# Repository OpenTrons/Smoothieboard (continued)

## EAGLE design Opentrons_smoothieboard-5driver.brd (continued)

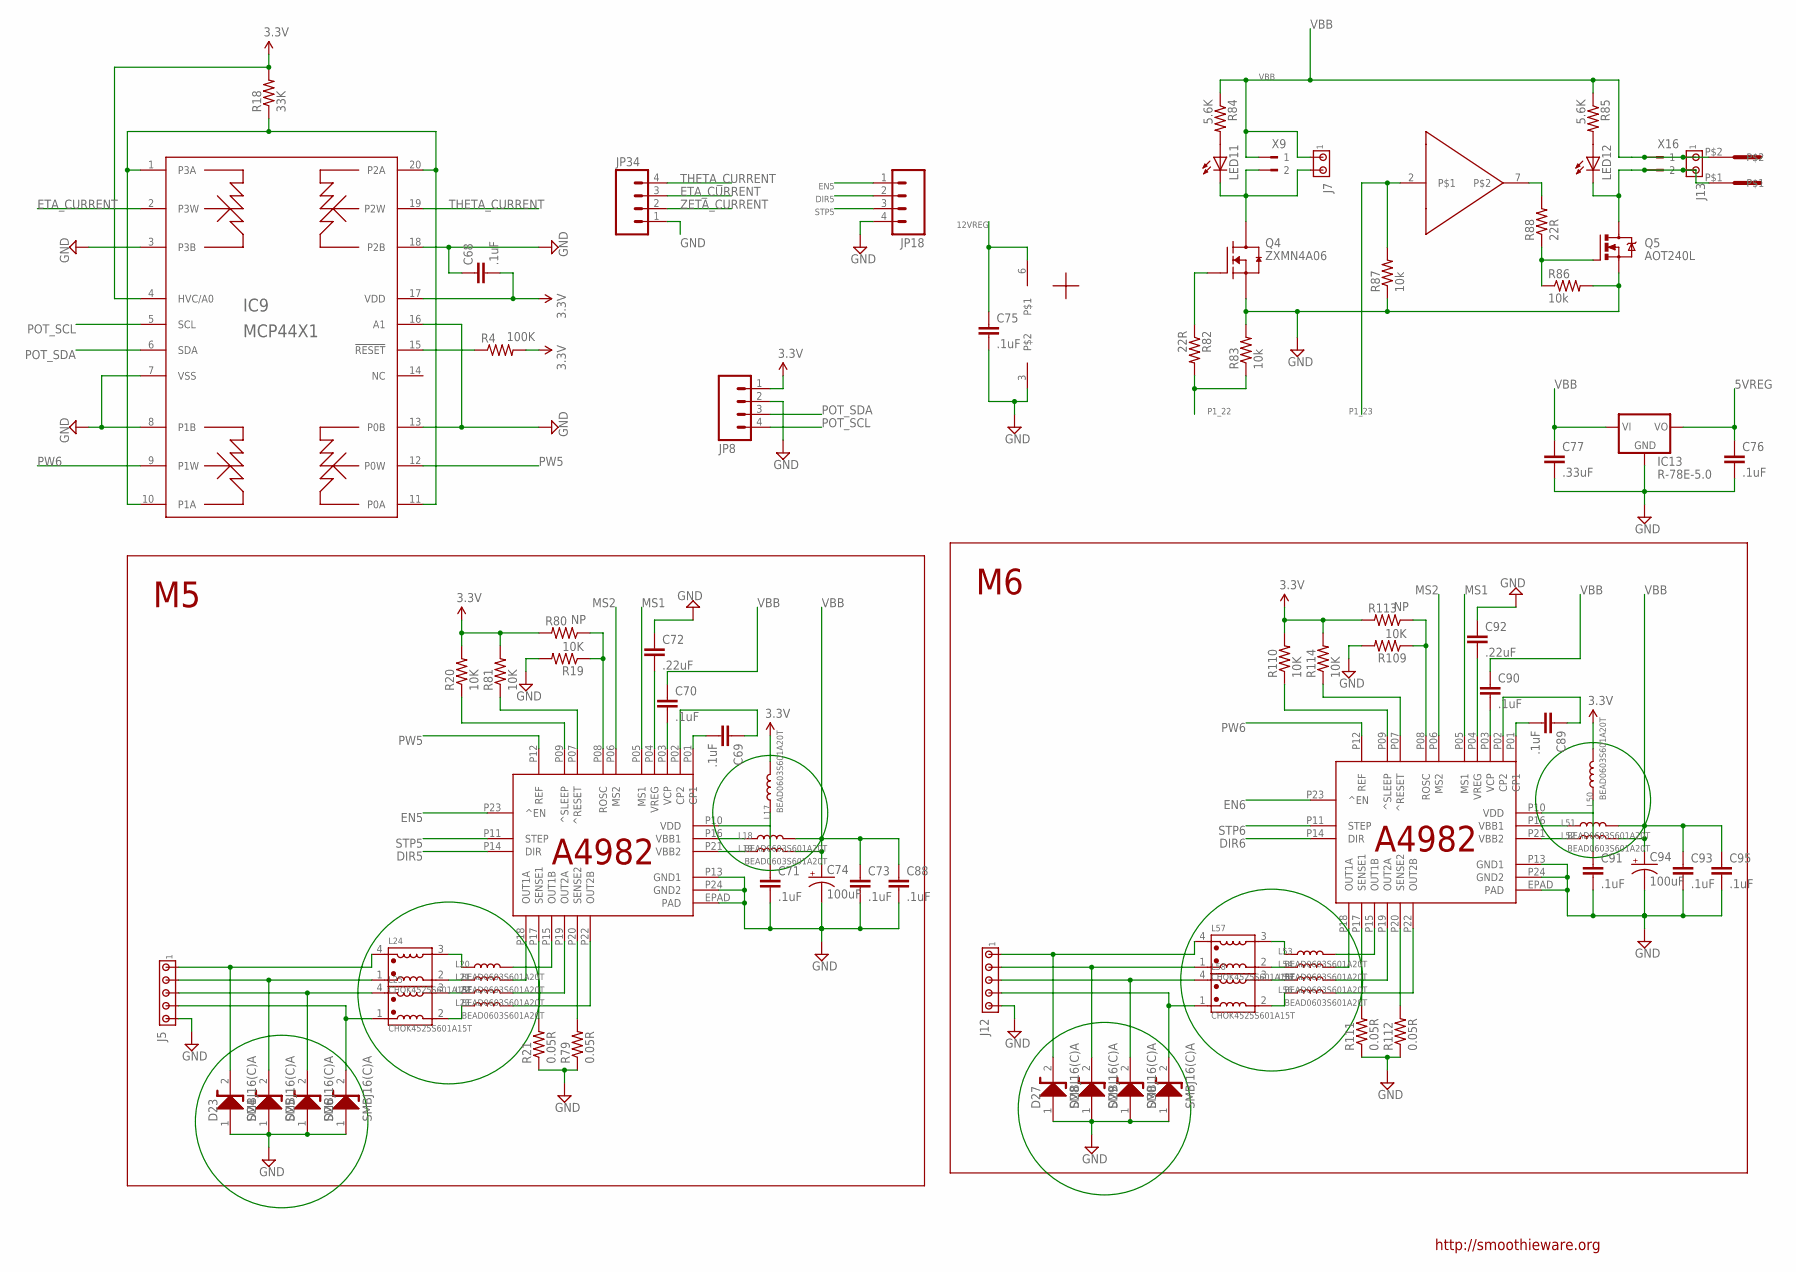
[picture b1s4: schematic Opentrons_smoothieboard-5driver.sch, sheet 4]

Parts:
C68, C69, C70, C71, C73, C75, C76, C88, C89, C90, C91, C93, C95: .1uF; C0603
C72, C92: .22uF; C0603
C74, C94: 100uF; PANASONIC_E
C77: .33uF; C0603
D23, D24, D25, D26, D27, D28, D29, D30: SMBJ16(C)A; DO214-AA_(SMB)
IC9: MCP44X1; TSSOP20
IC12, IC16: A4982; ETSSOP24
IC13: R-78E-5.0; R-78
IC15: TC4427; SOIC8
J5, J12: MTA05-100; 10X05MTA
J7, J13: MTA02-100; 10X02MTA
JP8, JP18, JP34: M041X04_NO_SILK; 1X04_NO_SILK
L17, L18, L19, L20, L21, L22, L23, L50, L51, L52, L53, L54, L55, L56: BEAD0603S601A20T; 0603(1608)
L24, L25, L57, L58: CHOK4525S601A15T; L-4525
LED11, LED12: LEDCHIP-LED0805; CHIP-LED0805
Q4: ZXMN4A06; SOT230P700X160-4N
Q5: AOT240L; TO220BV
R4: 100K; R0603
R18: 33K; R0603
R19, R20, R81, R109, R110, R114: 10K; R0603
R21, R79, R111, R112: 0.05R; R2512
R80, R113: NP; R0603
R82, R88: 22R; R0603
R83, R86, R87: 10k; R0603
R84, R85: 5.6K; R0603
U$7: 5MMCONN; 1715250000
X9, X16: 180G-2

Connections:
3.3V: C68.2, IC9.4 (HVC/A0), IC9.17 (VDD), JP8.1, L17.2, L50.2, R4.2, R18.2, R20.2, R80.2, R81.2, R110.2, R113.2, R114.2; also elsewhere on the board
5VREG: C76.1, IC13.3 (VO); also elsewhere on the board
12VREG: C75.1, IC15.6; also elsewhere on the board
DIR5: IC12.P14 (DIR), JP18.2; also elsewhere on the board
DIR6: IC16.P14 (DIR)
EN5: IC12.P23 (^EN), JP18.1; also elsewhere on the board
EN6: IC16.P23 (^EN)
ETA_CURRENT: IC9.2 (P3W), JP34.3
GND: C68.1, C71.2, C72.1, C73.2, C74.-, C75.2, C76.2, C77.2, C88.2, C91.2, C92.1, C93.2, C94.-, C95.2, D23.1 (A), D24.1 (A), D25.1 (A), D26.1 (A), D27.1 (A), D28.1 (A), D29.1 (A), D30.1 (A), IC9.3 (P3B), IC9.7 (VSS), IC9.8 (P1B), IC9.13 (P0B), IC9.16 (A1), IC9.18 (P2B), IC12.EPAD (PAD), IC12.P13 (GND1), IC12.P24 (GND2), IC13.2 (GND), IC15.3, IC16.EPAD (PAD), IC16.P13 (GND1), IC16.P24 (GND2), J5.5, J12.5, JP8.2, JP18.4, JP34.1, Q4.3 (S), Q5.S, R19.2, R21.1, R79.1, R83.2, R86.2, R87.1, R109.2, R111.1, R112.1; also elsewhere on the board
GPIO_FET1: Q5.G, R86.1, R88.1
J5_1A: D23.2 (K), J5.1, L24.4
J5_1A1: D27.2 (K), J12.1, L57.4
J5_1B: D24.2 (K), J5.2, L24.1
J5_1B1: D28.2 (K), J12.2, L57.1
J5_2A: D25.2 (K), J5.3, L25.4
J5_2A1: D29.2 (K), J12.3, L58.4
J5_2B: D26.2 (K), J5.4, L25.1
J5_2B1: D30.2 (K), J12.4, L58.1
MS1: IC12.P05 (MS1), IC16.P05 (MS1); also elsewhere on the board
MS2: IC12.P06 (MS2), IC16.P06 (MS2); also elsewhere on the board
unnamed: C89.2, IC16.P01 (CP1)
unnamed: IC9.15 (!RESET), R4.1
unnamed: J7.2, LED11.C, Q4.4 (D), X9.2
unnamed: IC9.1 (P3A), IC9.10 (P1A), IC9.11 (P0A), IC9.20 (P2A), R18.1
unnamed: C69.2, IC12.P01 (CP1)
unnamed: C69.1, IC12.P02 (CP2)
unnamed: C70.2, IC12.P03 (VCP)
unnamed: IC12.P17 (SENSE1), R21.2
unnamed: IC12.P20 (SENSE2), R79.2
unnamed: IC12.P18 (OUT1A), L21.2
unnamed: IC12.P15 (OUT1B), L20.2
unnamed: IC12.P19 (OUT2A), L22.2
unnamed: IC12.P22 (OUT2B), L23.2
unnamed: IC12.P08 (ROSC), R19.1, R80.1
unnamed: C72.2, IC12.P04 (VREG)
unnamed: IC12.P09 (^SLEEP), R20.1
unnamed: IC12.P07 (^RESET), R81.1
unnamed: Q4.1 (G), R82.1
unnamed: LED11.A, R84.2
unnamed: J13.2, LED12.C, Q5.D, U$7.P$1, X16.2
unnamed: LED12.A, R85.2
unnamed: IC15.7, R88.2
unnamed: C89.1, IC16.P02 (CP2)
unnamed: C71.1, IC12.P10 (VDD), L17.1
unnamed: IC12.P16 (VBB1), L18.1
unnamed: IC12.P21 (VBB2), L19.1
unnamed: L21.1, L24.2
unnamed: L20.1, L24.3
unnamed: L22.1, L25.3
unnamed: L23.1, L25.2
unnamed: C90.2, IC16.P03 (VCP)
unnamed: IC16.P17 (SENSE1), R111.2
unnamed: IC16.P20 (SENSE2), R112.2
unnamed: IC16.P18 (OUT1A), L54.2
unnamed: IC16.P15 (OUT1B), L53.2
unnamed: IC16.P19 (OUT2A), L55.2
unnamed: IC16.P22 (OUT2B), L56.2
unnamed: IC16.P08 (ROSC), R109.1, R113.1
unnamed: C92.2, IC16.P04 (VREG)
unnamed: IC16.P09 (^SLEEP), R110.1
unnamed: IC16.P07 (^RESET), R114.1
unnamed: C91.1, IC16.P10 (VDD), L50.1
unnamed: IC16.P16 (VBB1), L51.1
unnamed: IC16.P21 (VBB2), L52.1
unnamed: L54.1, L57.2
unnamed: L53.1, L57.3
unnamed: L55.1, L58.3
unnamed: L56.1, L58.2
P1_22: R82.2, R83.1; also elsewhere on the board
P1_23: IC15.2, R87.2; also elsewhere on the board
POT_SCL: IC9.5 (SCL), JP8.4; also elsewhere on the board
POT_SDA: IC9.6 (SDA), JP8.3; also elsewhere on the board
PW5: IC9.12 (P0W), IC12.P12 (REF)
PW6: IC9.9 (P1W), IC16.P12 (REF)
STP5: IC12.P11 (STEP), JP18.3; also elsewhere on the board
STP6: IC16.P11 (STEP)
THETA_CURRENT: IC9.19 (P2W), JP34.4
VBB: C70.1, C73.1, C74.+, C77.1, C88.1, C90.1, C93.1, C94.+, C95.1, IC13.1 (VI), J7.1, J13.1, L18.2, L19.2, L51.2, L52.2, R84.1, R85.1, U$7.P$2, X9.1, X16.1; also elsewhere on the board
ZETA_CURRENT: JP34.2

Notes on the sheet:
http://smoothieware.org

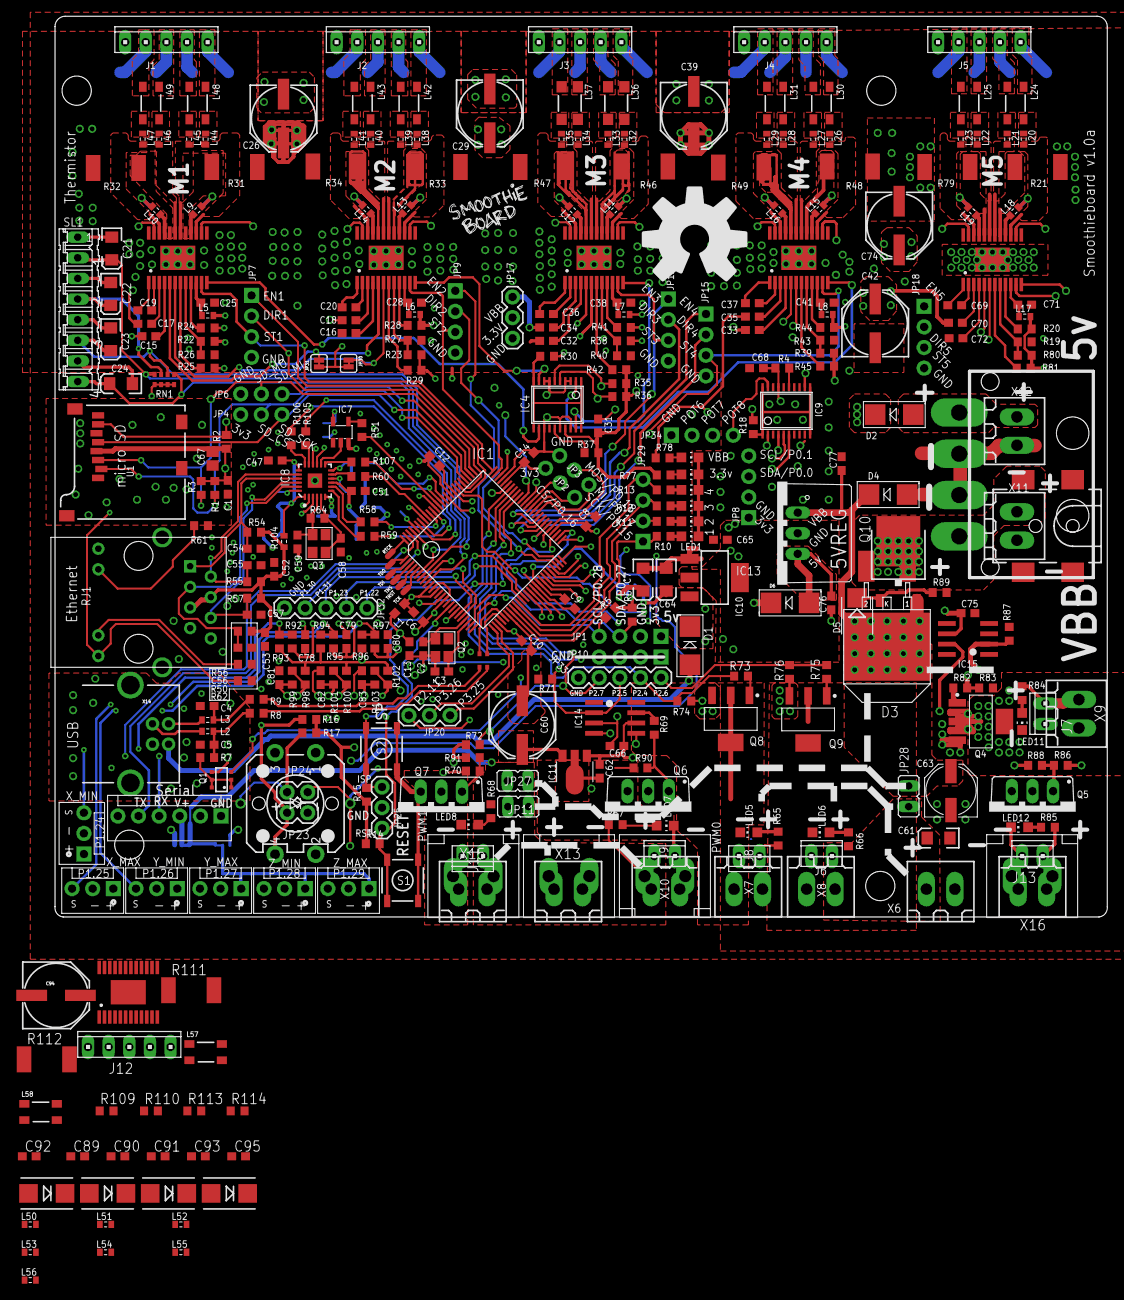
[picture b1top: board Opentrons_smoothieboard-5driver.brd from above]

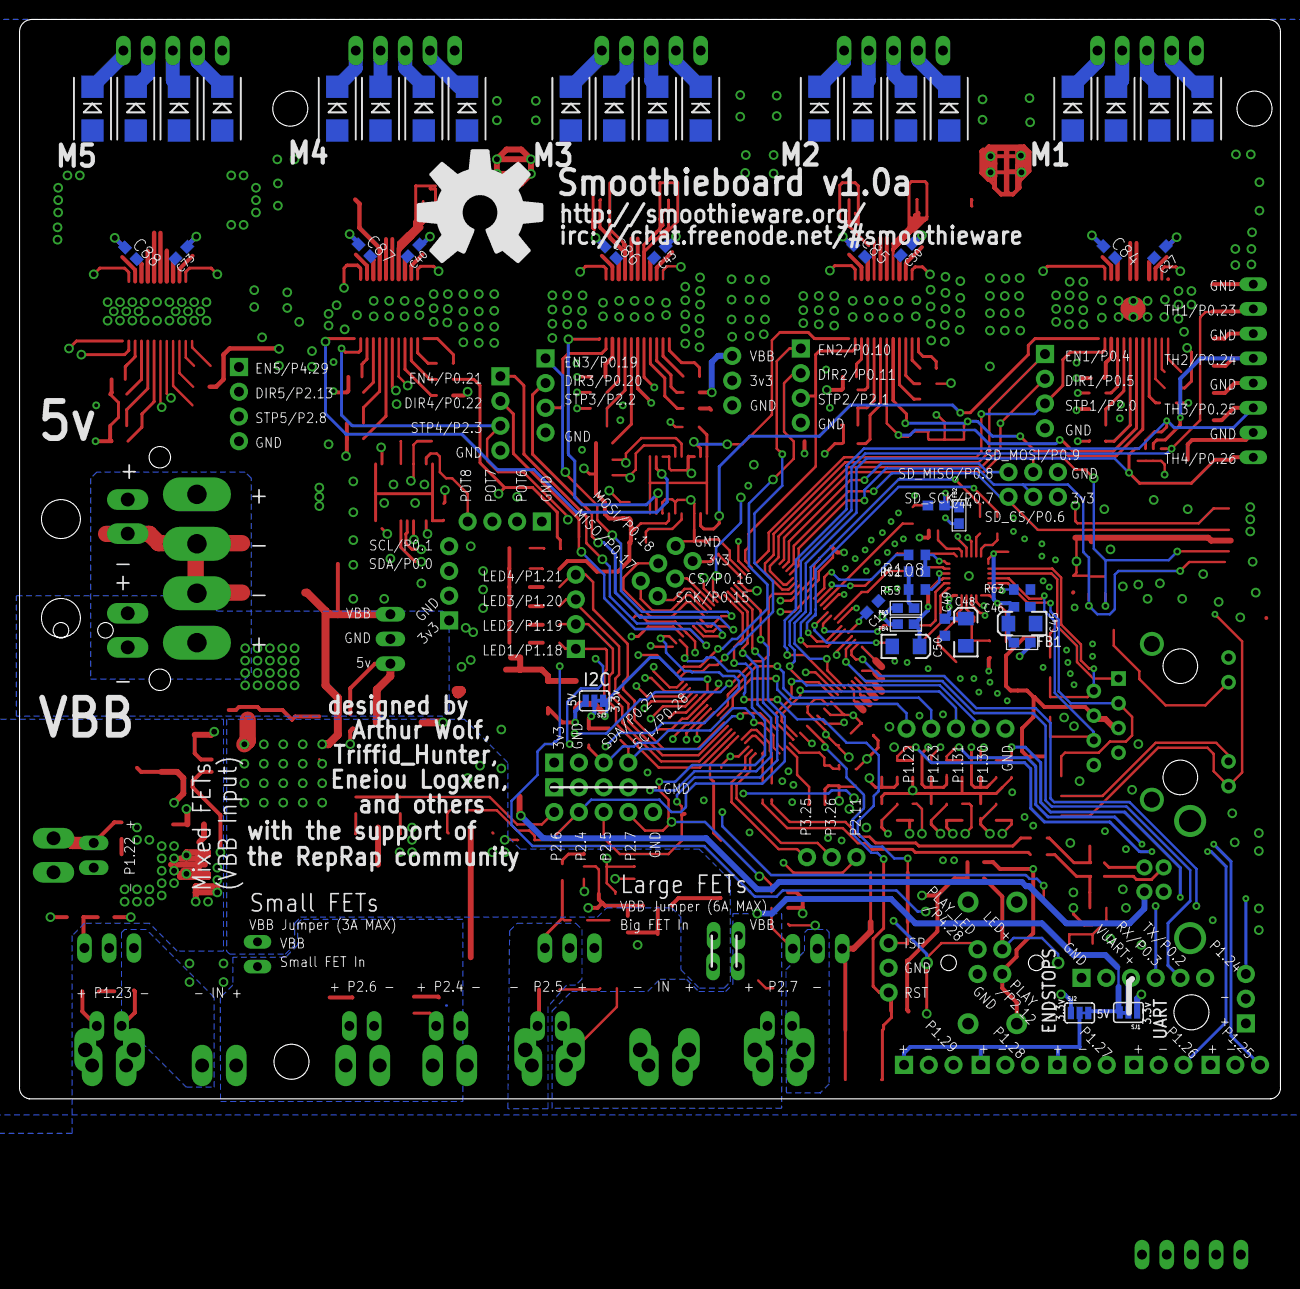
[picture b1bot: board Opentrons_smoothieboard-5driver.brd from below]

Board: 4 copper layers, 129.6 x 110.9 mm, 413 parts (49 on the bottom side), 316 nets.

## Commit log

2017-04-06 adds revisions from CE tests
2017-04-20 adds 6th driver
